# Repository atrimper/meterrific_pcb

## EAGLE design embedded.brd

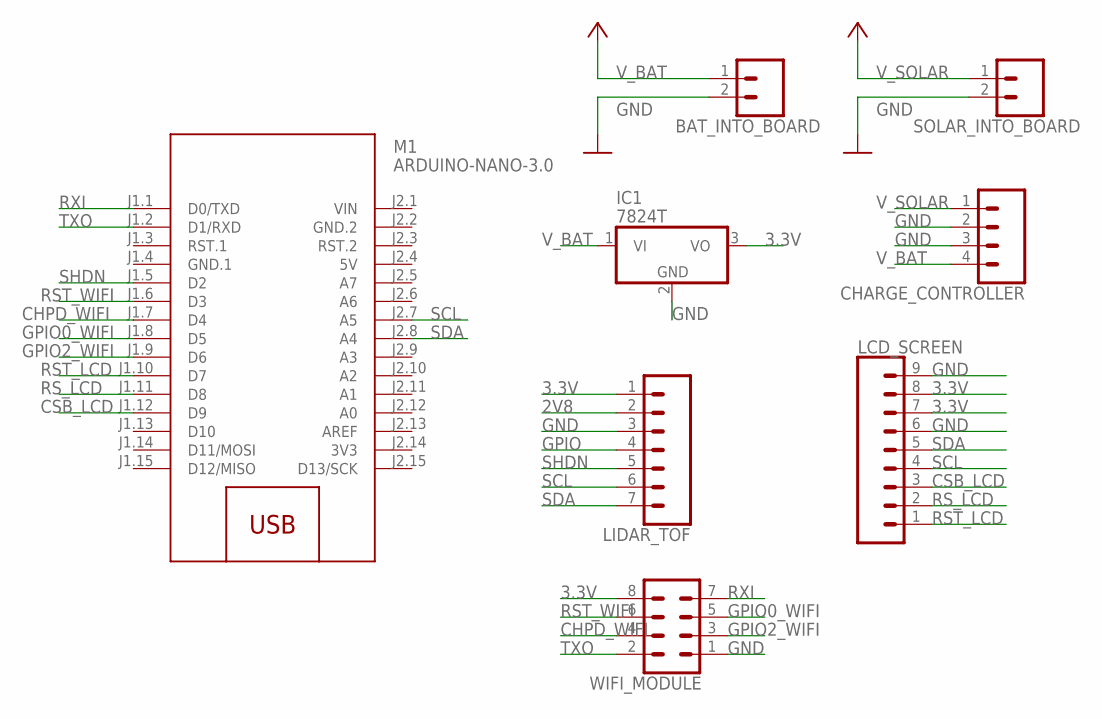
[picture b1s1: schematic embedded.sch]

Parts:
BAT_INTO_BOARD: CONN_02; 1X02
CHARGE_CONTROLLER: CONN_04; 1X04
IC1: 7824T; TO220H
LCD_SCREEN: CONN_09; 1X09
LIDAR_TOF: CONN_07; 1X07
M1: ARDUINO-NANO-3.0
SOLAR_INTO_BOARD: CONN_02; 1X02
WIFI_MODULE: CONN_04X2; 2X4

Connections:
2V8: LIDAR_TOF.2
3.3V: IC1.3 (VO), LCD_SCREEN.7, LCD_SCREEN.8, LIDAR_TOF.1, WIFI_MODULE.8
3V3: M1.J2.14 (3V3)
5V: M1.J2.4 (5V)
CHPD_WIFI: M1.J1.7 (D4), WIFI_MODULE.4
CSB_LCD: LCD_SCREEN.3, M1.J1.12 (D9)
GND: BAT_INTO_BOARD.2, CHARGE_CONTROLLER.2, CHARGE_CONTROLLER.3, IC1.2 (GND), LCD_SCREEN.6, LCD_SCREEN.9, LIDAR_TOF.3, SOLAR_INTO_BOARD.2, WIFI_MODULE.1
GND.1: M1.J1.4 (GND.1)
GND.2: M1.J2.2 (GND.2)
GPIO: LIDAR_TOF.4
GPIO0_WIFI: M1.J1.8 (D5), WIFI_MODULE.5
GPIO2_WIFI: M1.J1.9 (D6), WIFI_MODULE.3
RST_LCD: LCD_SCREEN.1, M1.J1.10 (D7)
RST_WIFI: M1.J1.6 (D3), WIFI_MODULE.6
RS_LCD: LCD_SCREEN.2, M1.J1.11 (D8)
RXI: M1.J1.1 (D0/TXD), WIFI_MODULE.7
SCL: LCD_SCREEN.4, LIDAR_TOF.6, M1.J2.7 (A5)
SDA: LCD_SCREEN.5, LIDAR_TOF.7, M1.J2.8 (A4)
SHDN: LIDAR_TOF.5, M1.J1.5 (D2)
TXO: M1.J1.2 (D1/RXD), WIFI_MODULE.2
VIN: M1.J2.1 (VIN)
V_BAT: BAT_INTO_BOARD.1, CHARGE_CONTROLLER.4, IC1.1 (VI)
V_SOLAR: CHARGE_CONTROLLER.1, SOLAR_INTO_BOARD.1

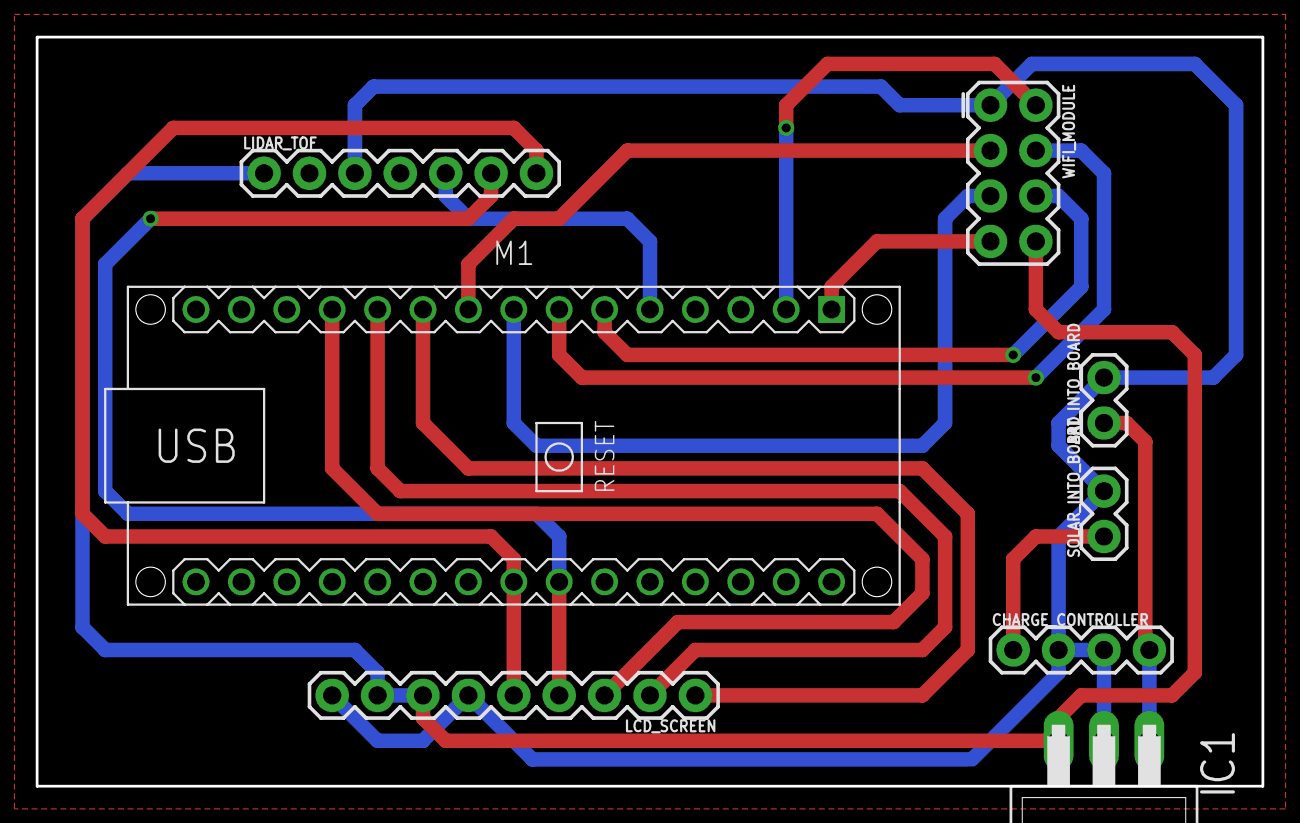
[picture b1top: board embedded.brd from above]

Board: 2 copper layers, 68.6 x 41.9 mm, 8 parts (0 on the bottom side), 16 nets.

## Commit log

2020-01-29 Initial commit of first produced pcb

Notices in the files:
parts and their libraries:
SparkFun-Connectors: Licensing: Creative Commons ShareAlike 4.0 International - https://creativecommons.org/licenses/by-sa/4.0
diy-modules: Released under the Creative Commons Attribution 4.0 International License: http://creativecommons.org/licenses/by/4.0
